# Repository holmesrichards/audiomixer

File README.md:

# Analog Output Audio Mixer

This is an audio mixer synth module in Kosmo format. It has three inputs, each with a slide attenuator, and a general level control and two identical outputs.

## Current draw
4 mA +12 V, 4 mA -12 V

## Photos

## Documentation:

* [Schematic](Docs/ao_audio_mixer.pdf)
* [PCB layout](Docs/ao_audio_mixer_layout.pdf)
* [BOM](Docs/ao_audio_mixer_bom.md)
* [Build notes](Docs/build.md)

## GitHub repository

* [https://github.com/holmesrichards/audiomixer](https://github.com/holmesrichards/audiomixer)

## Submodules

This repo uses submodules aoKicad and Kosmo_panel, which provide needed libaries for KiCad. To clone:

```
git clone git@github.com:holmesrichards/audiomixer.git
git submodule init
git submodule update
```

Alternatively do

```
git clone --recurse-submodules git@github.com:holmesrichards/audiomixer.git
```

Or if you download the repository as a zip file, you must also click on the "aoKicad" and "Kosmo\_panel" links on the GitHub page (they'll have "@ something" after them) and download them as separate zip files which you can unzip into this repo's aoKicad and Kosmo\_panel directories.

If desired, copy the files from aoKicad and Kosmo\_panel to wherever you prefer (your KiCad user library directory, for instance, if you have one). Then in KiCad, add symbol libraries 

```
aoKicad/ao_symbols
Kosmo_panel/Kosmo
```
and footprint libraries 
```
aoKicad/ao_tht
Kosmo_panel/Kosmo_panel.
```

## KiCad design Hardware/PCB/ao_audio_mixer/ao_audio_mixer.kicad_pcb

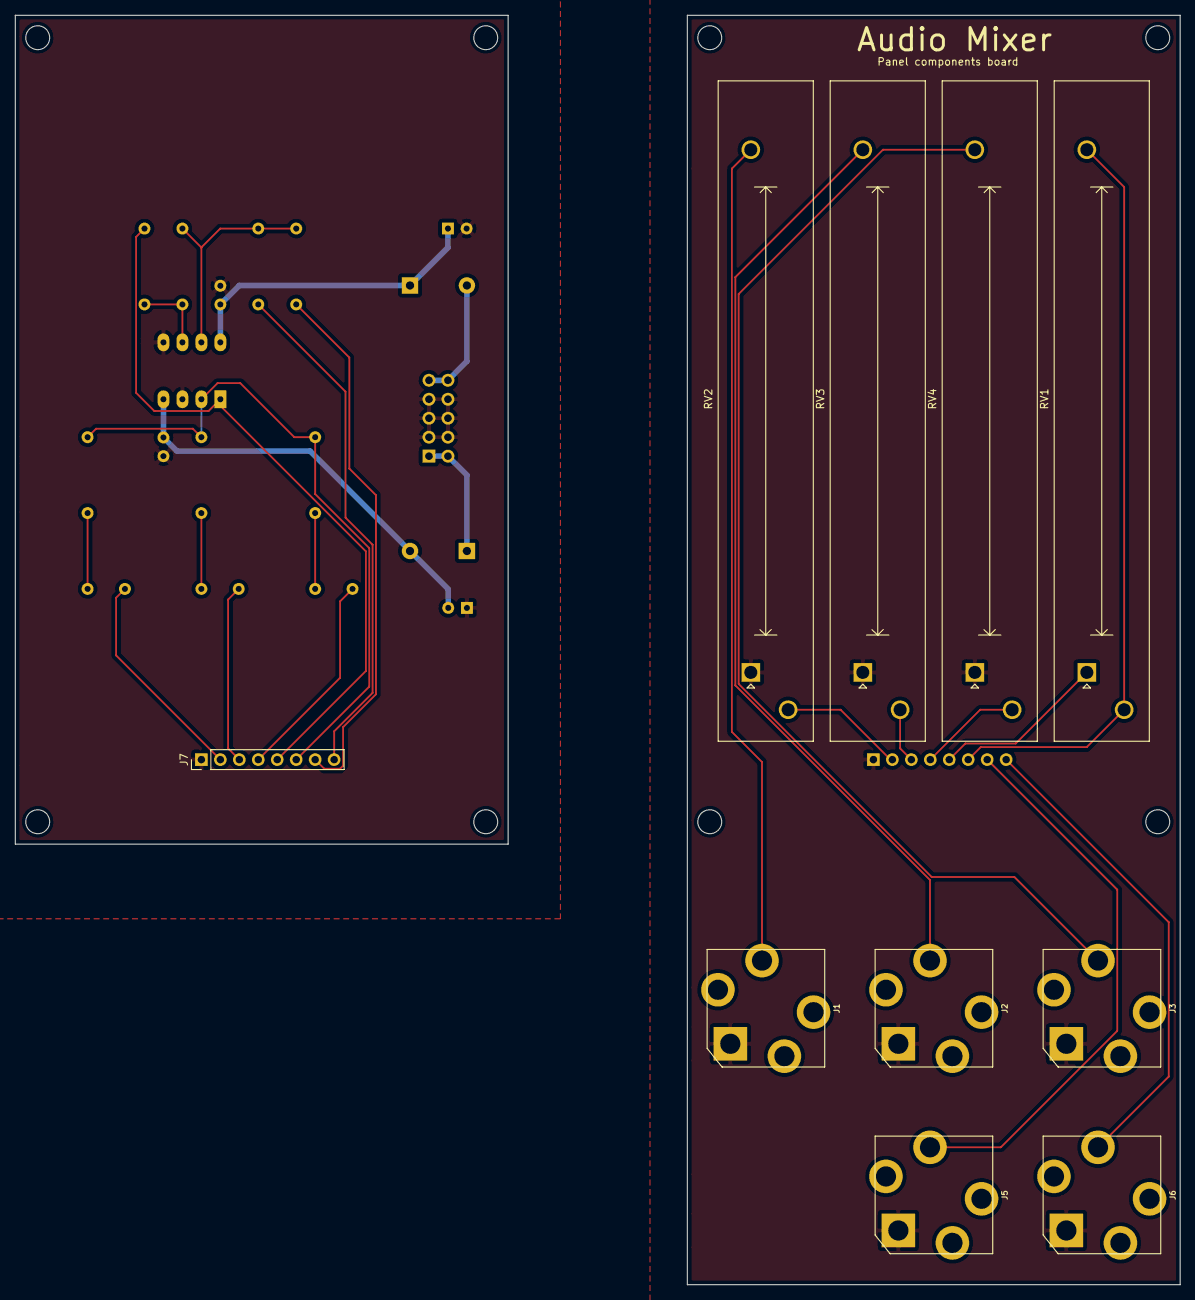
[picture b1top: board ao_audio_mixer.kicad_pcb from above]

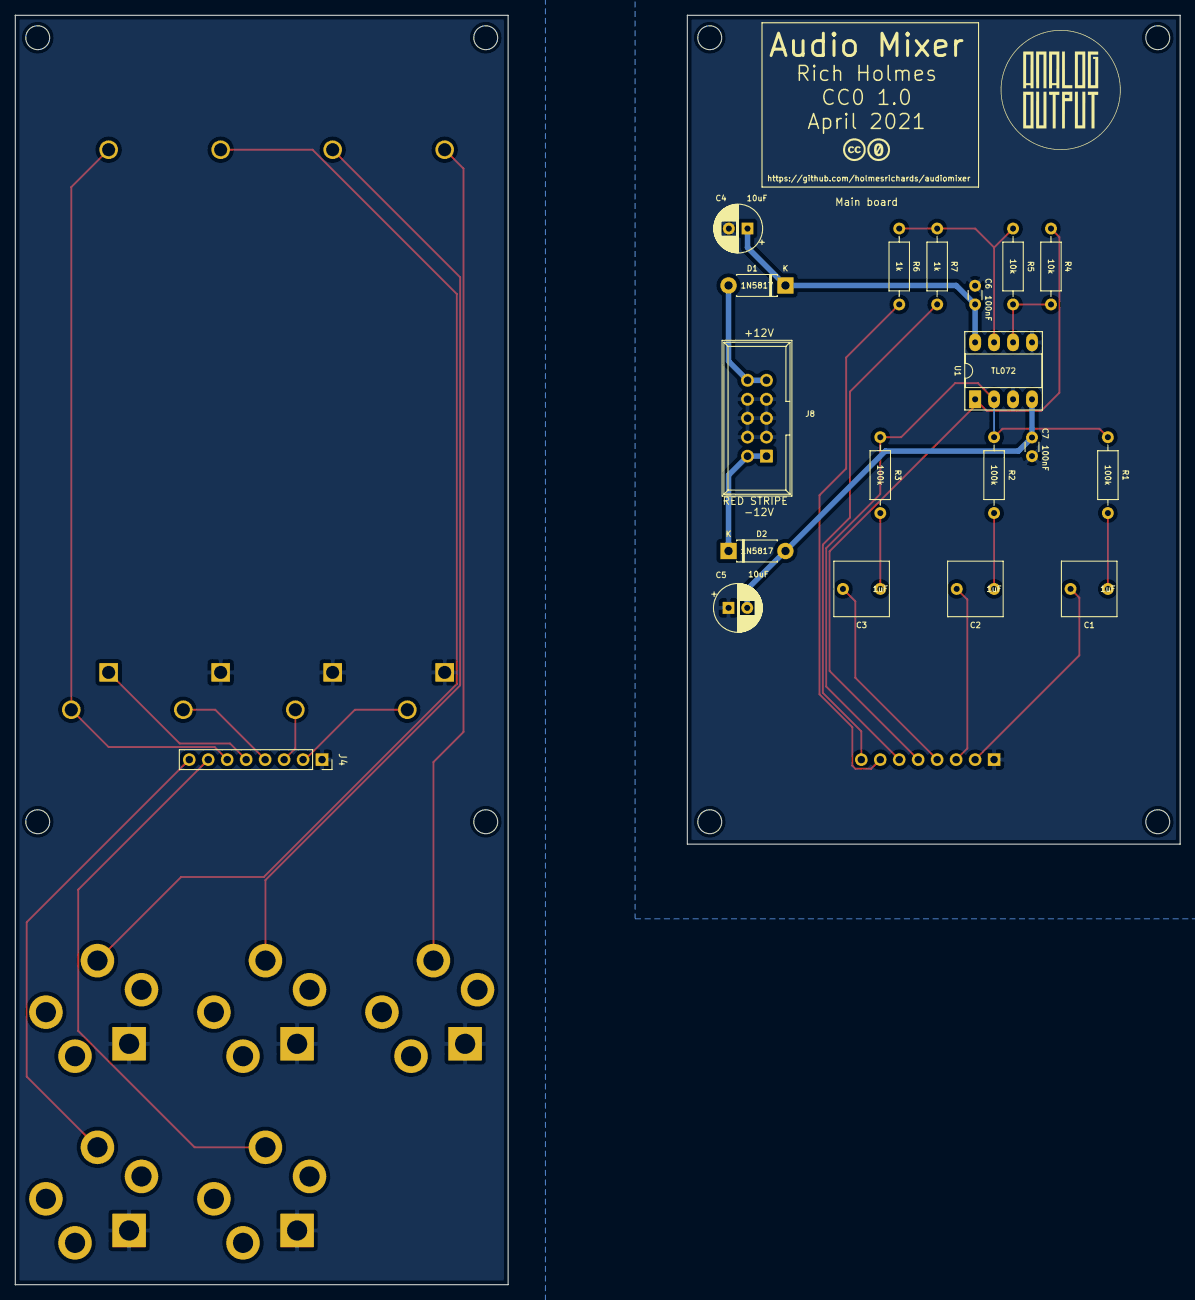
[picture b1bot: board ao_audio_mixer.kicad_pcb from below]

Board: 2 copper layers, 156.0 x 170.0 mm, 41 parts (25 on the bottom side), 28 nets.

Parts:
C1, C2, C3: 1uF; C_Rect_L7.2mm_W7.2mm_P5.00mm_FKS2_FKP2_MKS2_MKP2
C4, C5: 10uF; CP_Radial_D6.3mm_P2.50mm
C6, C7: 100nF; C_Disc_D3.0mm_W1.6mm_P2.50mm
D1, D2: 1N5817; D_DO-41_SOD81_P7.62mm_Horizontal
GRAF1, GRAF1#2: Panel holes; ao_audio_mixer_panel_slide_holes
GRAF2: AO Logo; analogoutput
GRAF3: CC0 Logo; CC0_logo
H1, H2, H3, H4, H5, H6, H7, H8: MountingHole; MountingHole_3.2mm_M3
J1, J2, J3, J5, J6: AudioJack2; Jack_6.35mm_PJ_629HAN
J4: Conn_01x08; PinSocket_1x08_P2.54mm_Vertical
J7: Conn_01x08; PinHeader_1x08_P2.54mm_Vertical
J8: Synth_power_2x5; Power_Header
R1, R2, R3: 100k; R_Axial_DIN0207_L6.3mm_D2.5mm_P10.16mm_Horizontal
R4, R5: 10k; R_Axial_DIN0207_L6.3mm_D2.5mm_P10.16mm_Horizontal
R6, R7: 1k; R_Axial_DIN0207_L6.3mm_D2.5mm_P10.16mm_Horizontal
RV1, RV2, RV3, RV4: A100k; Potentiometer_Alpha_RA6020F_Single_Slide
U1: TL072; DIP-8_W7.62mm_Socket_LongPads

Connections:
+12V: C4.1, C6.1, D1.1, U1.8
-12V: C5.2, C7.2, D2.2, U1.4
/+12_IN: D1.2, J8.9, J8.10
/-12_IN: D2.1, J8.1, J8.2
/IN1: J1.T, RV2.3
/IN2: J2.T, RV3.3
/IN3: J3.T, RV4.3
/OUT1P: J4.7, J5.T
/OUT2P: J4.8, J6.T
GND: C4.2, C5.1, C6.2, C7.1, J7.1, J8.3, J8.4, J8.5, J8.6, J8.7, J8.8, U1.3, U1.5
GND1: J1.S, J2.S, J3.S, J4.1, J5.S, J6.S, RV2.1, RV3.1, RV4.1
unnamed: C1.1, R1.2
unnamed: C1.2, J7.2
unnamed: C2.1, R2.2
unnamed: C2.2, J7.3
unnamed: C3.1, R3.2
unnamed: C3.2, J7.4
unnamed: J4.2, RV2.2
unnamed: J4.3, RV3.2
unnamed: J4.4, RV4.2
unnamed: J4.5, RV1.1
unnamed: J4.6, RV1.2, RV1.3
unnamed: J7.5, R4.2, U1.1
unnamed: J7.6, R1.1, R2.1, R3.1, U1.2
unnamed: R4.1, R5.2, U1.6
unnamed: R5.1, R6.2, R7.2, U1.7
OUT1: J7.7, R6.1
OUT2: J7.8, R7.1

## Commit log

2021-08-07 Initial version
2021-08-07 Final tweaks before fabbing
2021-08-12 submodules
2021-08-12 Create LICENSE
2021-08-12 README
2021-08-12 update kicad_panel
2021-08-12 board mount jacks
2021-08-16 Restore deleted board
2021-08-21 relocate libraries
2021-08-21 rm project libraries
2021-08-27 submodule doc
2021-08-28 Documentation and final fixes before release
2021-08-28 add back lost link
2021-09-09 Clean up libraries, Schottky footprint update
2021-09-15 SVG decontamination
2021-12-24 Current draw
